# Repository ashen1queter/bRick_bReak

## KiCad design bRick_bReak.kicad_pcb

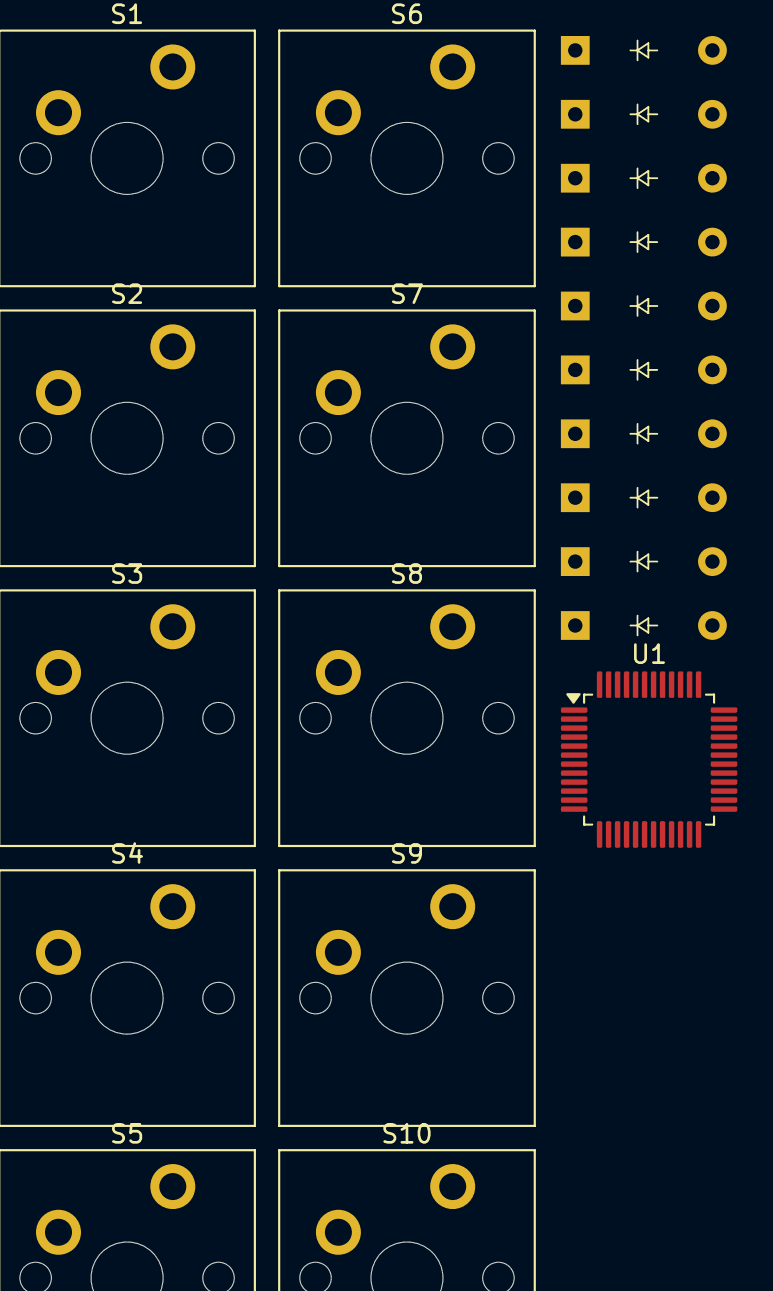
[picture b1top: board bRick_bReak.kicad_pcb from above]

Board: 2 copper layers, 21 parts (0 on the bottom side), 18 nets, no tracks yet.

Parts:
D1, D2, D3, D4, D5, D6, D7, D8, D9, D10: Diode; Diode_DO-35
S1, S2, S3, S4, S5, S6, S7, S8, S9, S10: Keyswitch; MX_PCB_1.00u
U1: STM32F103C8Tx; LQFP-48_7x7mm_P0.5mm

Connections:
Col 0: S1.1, S6.1, U1.12 (PA2)
Col 1: S2.1, S7.1, U1.13 (PA3)
Col 2: S3.1, S8.1, U1.14 (PA4)
Col 3: S4.1, S9.1, U1.15 (PA5)
Col 4: S5.1, S10.1, U1.16 (PA6)
unnamed: D1.2 (A), S1.2
unnamed: D2.2 (A), S2.2
unnamed: D3.2 (A), S3.2
unnamed: D4.2 (A), S4.2
unnamed: D5.2 (A), S5.2
unnamed: D6.2 (A), S6.2
unnamed: D7.2 (A), S7.2
unnamed: D8.2 (A), S8.2
unnamed: D9.2 (A), S9.2
unnamed: D10.2 (A), S10.2
unnamed: U1.23 (VSS), U1.35 (VSS), U1.47 (VSS)
Row 0: D1.1 (K), D2.1 (K), D3.1 (K), D4.1 (K), D5.1 (K), U1.10 (PA0)
Row 1: D6.1 (K), D7.1 (K), D8.1 (K), D9.1 (K), D10.1 (K), U1.11 (PA1)

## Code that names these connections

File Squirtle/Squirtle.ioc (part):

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Mcu.Name=STM32F103C(8-B)Tx
Mcu.Package=LQFP48
Mcu.UserName=STM32F103C8Tx
PA0-WKUP.GPIOParameters=GPIO_PuPd,GPIO_Label
PA0-WKUP.GPIO_Label=R1
PA0-WKUP.GPIO_PuPd=GPIO_PULLUP
PA0-WKUP.Signal=GPIO_Input
PA1.GPIOParameters=GPIO_PuPd,GPIO_Label
PA1.GPIO_Label=R2
PA1.GPIO_PuPd=GPIO_PULLUP
PA1.Signal=GPIO_Input
PA10.Mode=Asynchronous
PA10.Signal=USART1_RX
PA2.GPIOParameters=GPIO_PuPd,GPIO_Label
PA2.GPIO_Label=C1
PA2.GPIO_PuPd=GPIO_PULLUP
PA2.Signal=GPIO_Input
PA3.GPIOParameters=GPIO_PuPd,GPIO_Label
PA3.GPIO_Label=C2
PA3.GPIO_PuPd=GPIO_PULLUP
PA3.Signal=GPIO_Input
PA4.GPIOParameters=GPIO_PuPd,GPIO_Label
PA4.GPIO_Label=C3
PA4.GPIO_PuPd=GPIO_PULLUP
PA4.Signal=GPIO_Input
PA5.GPIOParameters=GPIO_PuPd,GPIO_Label
PA5.GPIO_Label=C4
PA5.GPIO_PuPd=GPIO_PULLUP
PA5.Signal=GPIO_Input
PA6.GPIOParameters=GPIO_PuPd,GPIO_Label
PA6.GPIO_Label=C5
PA6.GPIO_PuPd=GPIO_PULLUP
PA6.Signal=GPIO_Input
PA9.Mode=Asynchronous
PA9.Signal=USART1_TX
board=custom

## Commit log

2025-04-05 Layout and Plate proto design
2025-04-05 Receiver MCU
2025-04-05 Sender MCU
2025-04-05 Deleted Pikachu and Ash proto code folders
2025-04-05 Deleted proto code and pika is main MCU
2025-04-05 Updated only pika code proto, rest are just bases
2025-04-05 Updated only pika code proto, rest are just bases, again
2025-04-05 Updated only pika code proto, rest are just bases, again, again
2025-04-06 Proto codes for all updated
2025-04-06 Proto codes for all updated, again
2025-04-06 Done for day
2025-04-09 Layout edit
2025-04-09 Fixed minor stuff
2025-04-09 Fixed some syntax issues
2025-04-09 Fixed some more syntax issues
2025-04-09 Header names written
2025-04-09 L-Shift byte activation code written, de-activation code must be written
2025-04-09 De-activation code written and fixed many syntax issues
2025-04-09 De-activation code fixed and fixed many syntax issues
2025-04-09 Added proto resume
2025-04-11 Private functions syntax error kinda resolved
2025-04-11 Toying with CMake
2025-04-11 Toying with Linker script
2025-04-11 Confused
2025-04-20 Few synatx issues solved
2025-04-20 Few syntax issues solved
2025-04-25 KiCad stuff and scotto keeb git added
2025-04-25 Working on power off
